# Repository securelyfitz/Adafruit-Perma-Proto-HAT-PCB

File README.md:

# Raspberry Pi SAO Hat
hastily derived from the Adafruit-Perma-Proto-HAT-PCB

PCB files for the Adafruit Perma Proto HAT with the proto area removed and replaced with SAO headers

Format is EagleCAD schematic and board layout

For more details, check out the product page at

-----> https://www.adafruit.com/products/2310

-----> https://www.adafruit.com/products/2314

Adafruit invests time and resources providing this open source design, 
please support Adafruit and open-source hardware by purchasing 
products from Adafruit!

Designed by Adafruit Industries.  
Creative Commons Attribution, Share-Alike license, check license.txt for more information
All text above must be included in any redistribution
Defiled by @securelyfitz.

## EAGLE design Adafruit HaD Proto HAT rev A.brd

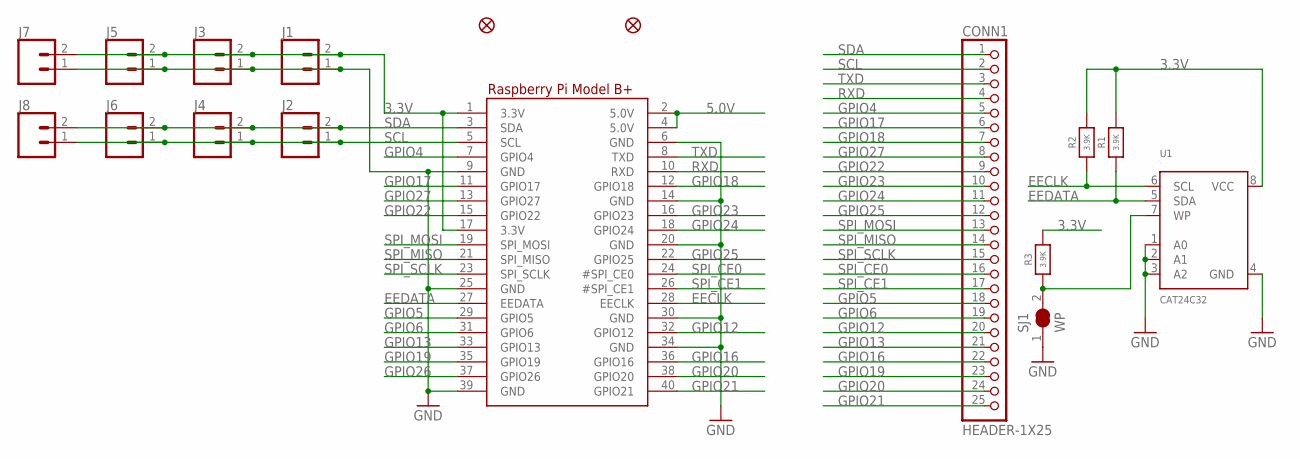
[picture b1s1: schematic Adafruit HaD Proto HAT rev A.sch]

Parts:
CONN1: HEADER-1X25; 1X25_ROUND_70MIL
FID2, FID3: FIDUCIAL""; FIDUCIAL_1MM
J1, J2, J3, J4, J5, J6, J7, J8: CONN_02LOCK; 1X02_LOCK
R1, R2, R3: 3.9K; 0805-NO
RPI1: RASPBERRYPI_BPLUS_HATNOSLOTS; PI_HAT_NOSLOTS
SJ1: WP; SOLDERJUMPER_CLOSEDWIRE
U1: CAT24C32; SOIC8_150MIL

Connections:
3.3V: J1.2, J3.2, J5.2, J7.2, R1.2, R2.2, R3.2, RPI1.1 (3.3V), RPI1.17 (3.3V), U1.8 (VCC)
5.0V: RPI1.2 (5.0V), RPI1.4 (5.0V)
EECLK: R2.1, RPI1.28 (EECLK), U1.6 (SCL)
EEDATA: R1.1, RPI1.27 (EEDATA), U1.5 (SDA)
GND: J1.1, J3.1, J5.1, J7.1, RPI1.6 (GND), RPI1.9 (GND), RPI1.14 (GND), RPI1.20 (GND), RPI1.25 (GND), RPI1.30 (GND), RPI1.34 (GND), RPI1.39 (GND), SJ1.1, U1.1 (A0), U1.2 (A1), U1.3 (A2), U1.4 (GND)
GPIO4: CONN1.5, RPI1.7 (GPIO4)
GPIO5: CONN1.18, RPI1.29 (GPIO5)
GPIO6: CONN1.19, RPI1.31 (GPIO6)
GPIO12: CONN1.20, RPI1.32 (GPIO12)
GPIO13: CONN1.21, RPI1.33 (GPIO13)
GPIO16: CONN1.22, RPI1.36 (GPIO16)
GPIO17: CONN1.6, RPI1.11 (GPIO17)
GPIO18: CONN1.7, RPI1.12 (GPIO18)
GPIO19: CONN1.23, RPI1.35 (GPIO19)
GPIO20: CONN1.24, RPI1.38 (GPIO20)
GPIO21: CONN1.25, RPI1.40 (GPIO21)
GPIO22: CONN1.9, RPI1.15 (GPIO22)
GPIO23: CONN1.10, RPI1.16 (GPIO23)
GPIO24: CONN1.11, RPI1.18 (GPIO24)
GPIO25: CONN1.12, RPI1.22 (GPIO25)
GPIO26: RPI1.37 (GPIO26)
GPIO27: CONN1.8, RPI1.13 (GPIO27)
unnamed: R3.1, SJ1.2, U1.7 (WP)
RXD: CONN1.4, RPI1.10 (RXD)
SCL: CONN1.2, J2.1, J4.1, J6.1, J8.1, RPI1.5 (SCL)
SDA: CONN1.1, J2.2, J4.2, J6.2, J8.2, RPI1.3 (SDA)
SPI_CE0: CONN1.16, RPI1.24 (#SPI_CE0)
SPI_CE1: CONN1.17, RPI1.26 (#SPI_CE1)
SPI_MISO: CONN1.14, RPI1.21 (SPI_MISO)
SPI_MOSI: CONN1.13, RPI1.19 (SPI_MOSI)
SPI_SCLK: CONN1.15, RPI1.23 (SPI_SCLK)
TXD: CONN1.3, RPI1.8 (TXD)

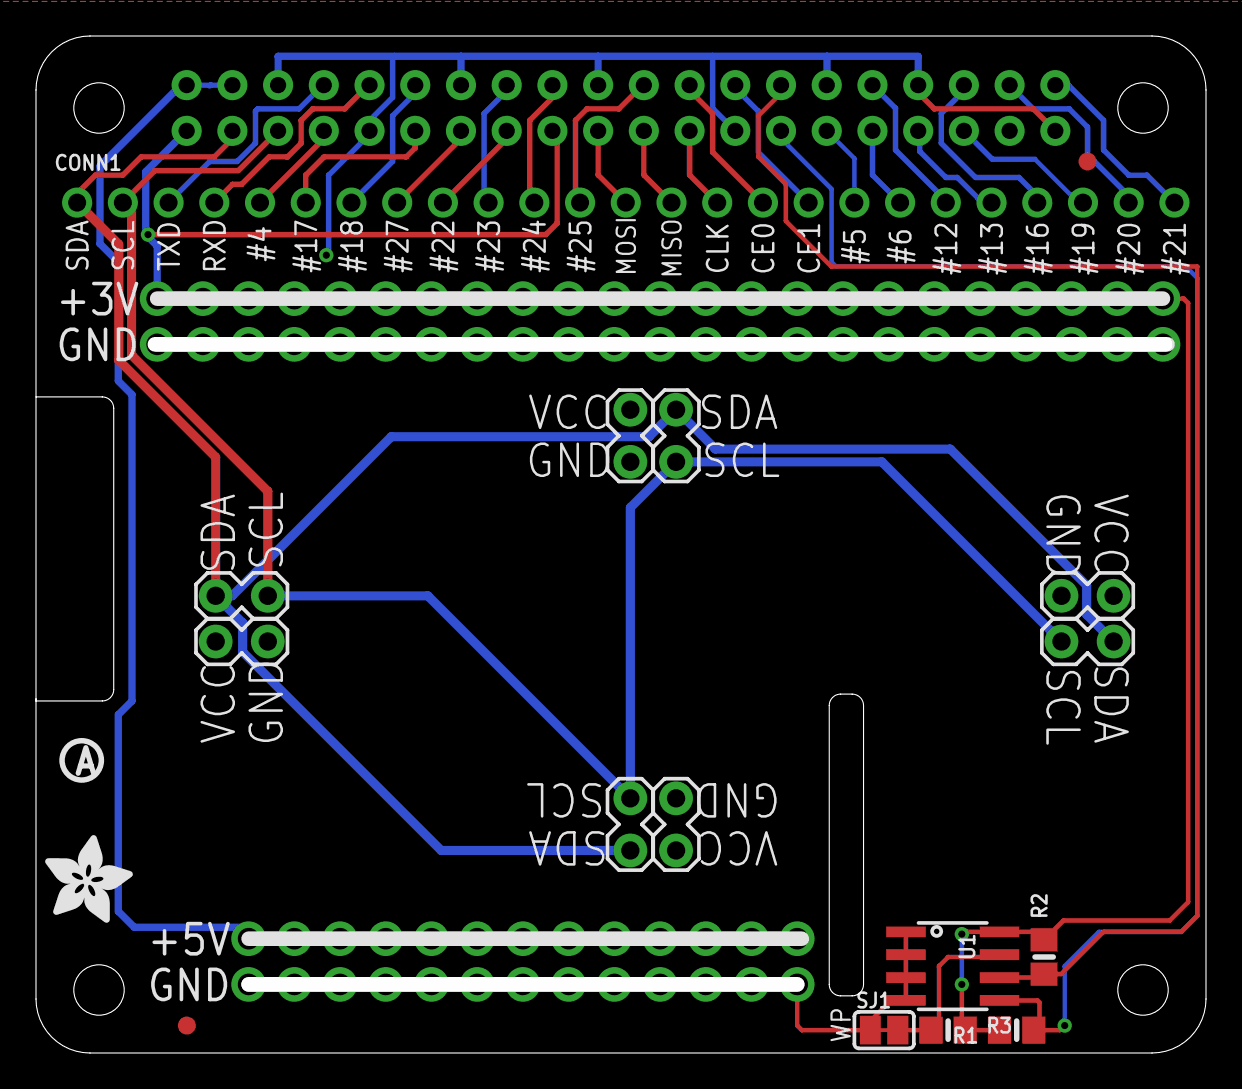
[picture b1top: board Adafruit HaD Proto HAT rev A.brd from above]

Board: 2 copper layers, 65.0 x 56.5 mm, 19 parts (0 on the bottom side), 31 nets.

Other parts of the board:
U$1: ADAFRUIT_5MM
U$3: PCBFEAT-REV-056

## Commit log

2018-07-30 ripped out proto area, added in 4xSAO connectors

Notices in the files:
parts and their libraries:
microbuilder: This work is placed in the public domain, and may be freely used for commercial and non-commercial work with the following conditions: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
SparkFun-Connectors: Licensing: Creative Commons ShareAlike 4.0 International - https://creativecommons.org/licenses/by-sa/4.0
